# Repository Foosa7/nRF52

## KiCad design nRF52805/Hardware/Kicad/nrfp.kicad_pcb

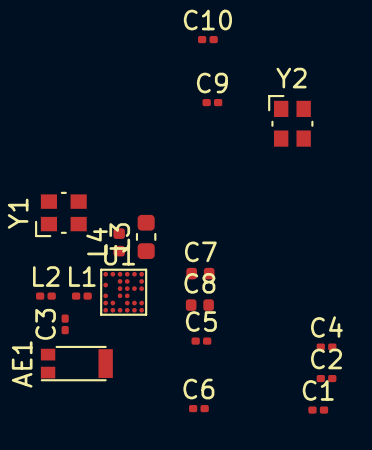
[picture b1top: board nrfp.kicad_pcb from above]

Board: 2 copper layers, 18 parts (0 on the bottom side), 14 nets, no tracks yet.

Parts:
AE1: Antenna_Chip; Pulse_W3011
C1, C2, C9, C10: 12pF; C_0201_0603Metric
C3: 1.2pF; C_0201_0603Metric
C4, C5: 100nF; C_0201_0603Metric
C6: 100pF; C_0201_0603Metric
C7: 2.2uF; C_0402_1005Metric
C8: 1uF; C_0402_1005Metric
L1: 2.2nH; L_0201_0603Metric
L2: 3.3nH; L_0201_0603Metric
L3: 10uH; L_0603_1608Metric
L4: 15nH; L_0402_1005Metric
U1: nRF52805; WLCSP_Nordic
Y1: 32kHz; Crystal_SMD_Abracon_ABM10-4Pin_2.5x2.0mm
Y2: 32.768kHz; Crystal_SMD_Abracon_ABM10-4Pin_2.5x2.0mm

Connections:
DEC1: C4.1, U1.B6
unnamed: AE1.1, L2.2
unnamed: C3.1, L1.2, L2.1
unnamed: C5.1, U1.G6
unnamed: C6.2, C8.1, L4.1, U1.A3, U1.A4
unnamed: L1.1, U1.E1
unnamed: L3.1, L4.2
unnamed: L3.2, U1.A5
VDD: C7.1, U1.A6
VSS_PA: C1.2, C2.2, C3.2, C4.2, C5.2, C6.1, C7.2, C8.2, C9.2, C10.2, U1.B3, U1.B4, U1.C1, U1.D3, U1.D4, U1.E3, U1.E4
XC1: C1.1, U1.A1, Y1.1
XC2: C2.1, U1.A2, Y1.2
XL1: C9.1, U1.D6, Y2.1
XL2: C10.1, U1.D5, Y2.2
